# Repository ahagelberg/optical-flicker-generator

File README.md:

# Optical Flicker Generator

Optical Flicker Generator is a complete hardware + firmware device for controlled high-power optical stimulation.

Current hardware platform:

- Arduino MKR Zero
- Arduino Ethernet Shield
- Custom PCB with high-current LED driver stages

Current software provides:

- Web control page (`/`)
- Web configuration page (`/config`)
- HTTP JSON API
- ASCII shell over Serial and optional Telnet

## Project Scope

- Firmware source code is under `firmware/`.
- Hardware design files (schematics/PCB/manufacturing outputs) are under `hardware/`.

## Documentation

- User manual: `firmware/USER_MANUAL.md`
- Interface/protocol reference: `firmware/PROTOCOL.md`

## Getting Started

1. Flash the firmware to the device.
2. Connect power and Ethernet.
3. Open the control page in a browser using:
   - `http://flicker-<suffix>.local/`, or
   - the IP shown on the device display.

## Repository Layout

- `firmware/` - PlatformIO firmware source and documentation
- `hardware/` - Hardware design files

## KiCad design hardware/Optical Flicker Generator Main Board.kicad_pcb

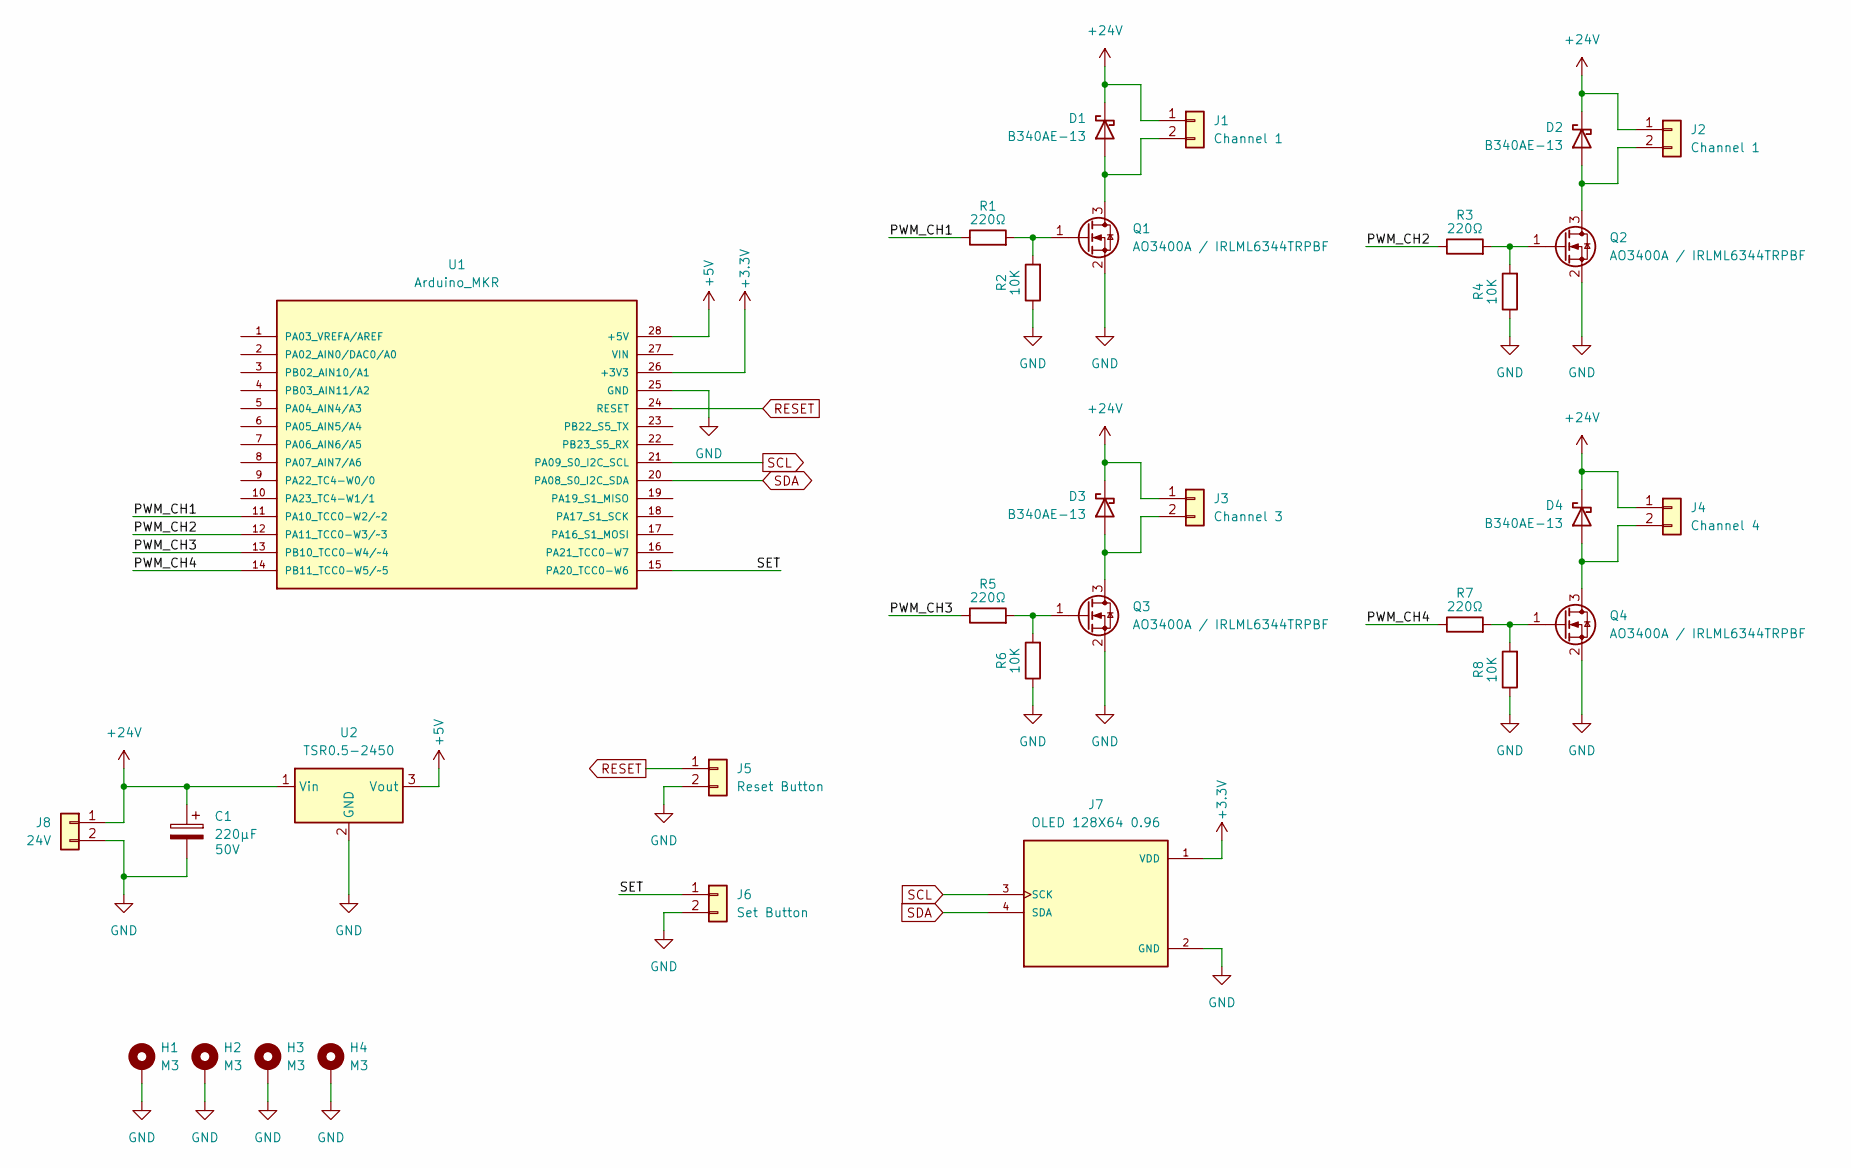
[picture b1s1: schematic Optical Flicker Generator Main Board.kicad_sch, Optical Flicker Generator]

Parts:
C1: 220μF; CP_Elec_10x10.5; Voltage 50V
D1, D2, D3, D4: B340AE-13; D_SMA
H1, H2, H3, H4: M3; MountingHole_3.2mm_M3_Pad
J1, J2: Channel 1; JST_XH_B2B-XH-A_1x02_P2.50mm_Vertical
J3: Channel 3; JST_XH_B2B-XH-A_1x02_P2.50mm_Vertical
J4: Channel 4; JST_XH_B2B-XH-A_1x02_P2.50mm_Vertical
J5: Reset Button; JST_XH_B2B-XH-A_1x02_P2.50mm_Vertical
J6: Set Button; JST_XH_B2B-XH-A_1x02_P2.50mm_Vertical
J7: OLED 128X64 0.96; JST_XH_B4B-XH-A_1x04_P2.50mm_Vertical; PARTREV NA
J8: 24V; JST_XH_B2B-XH-A_1x02_P2.50mm_Vertical
Q1, Q2, Q3, Q4: AO3400A / IRLML6344TRPBF; SOT-23
R1, R3, R5, R7: 220Ω; R_0805_2012Metric
R2, R4, R6, R8: 10K; R_0805_2012Metric
U1: Arduino_MKR; PARTREV 5
U2: TSR0.5-2450; Converter_DCDC_TRACO_TSR0.5-24xx_TSR0.5-24xxx_THT

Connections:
+3.3V: J7.1 (VDD), U1.26 (+3V3)
+5V: U1.28 (+5V), U2.3 (Vout)
+24V: C1.1, D1.1 (K), D2.1 (K), D3.1 (K), D4.1 (K), J1.1, J2.1, J3.1, J4.1, J8.1, U2.1 (Vin)
/PWM_CH1: R1.1, U1.11 (PA10_TCC0-W2/~2)
/PWM_CH2: R3.1, U1.12 (PA11_TCC0-W3/~3)
/PWM_CH3: R5.1, U1.13 (PB10_TCC0-W4/~4)
/PWM_CH4: R7.1, U1.14 (PB11_TCC0-W5/~5)
/SET: J6.1, U1.15 (PA20_TCC0-W6)
GND: C1.2, H1.1 (1_1), H2.1 (1_1), H3.1 (1_1), H4.1 (1_1), J5.2, J6.2, J7.2 (GND), J8.2, Q1.2 (S), Q2.2 (S), Q3.2 (S), Q4.2 (S), R2.1, R4.1, R6.1, R8.1, U1.25 (GND), U2.2 (GND)
unnamed: D1.2 (A), J1.2, Q1.3 (D)
unnamed: D2.2 (A), J2.2, Q2.3 (D)
unnamed: D3.2 (A), J3.2, Q3.3 (D)
unnamed: D4.2 (A), J4.2, Q4.3 (D)
unnamed: Q1.1 (G), R1.2, R2.2
unnamed: Q2.1 (G), R3.2, R4.2
unnamed: Q3.1 (G), R5.2, R6.2
unnamed: Q4.1 (G), R7.2, R8.2
RESET: J5.1, U1.24 (RESET)
SCL: J7.3 (SCK), U1.21 (PA09_S0_I2C_SCL)
SDA: J7.4 (SDA), U1.20 (PA08_S0_I2C_SDA)

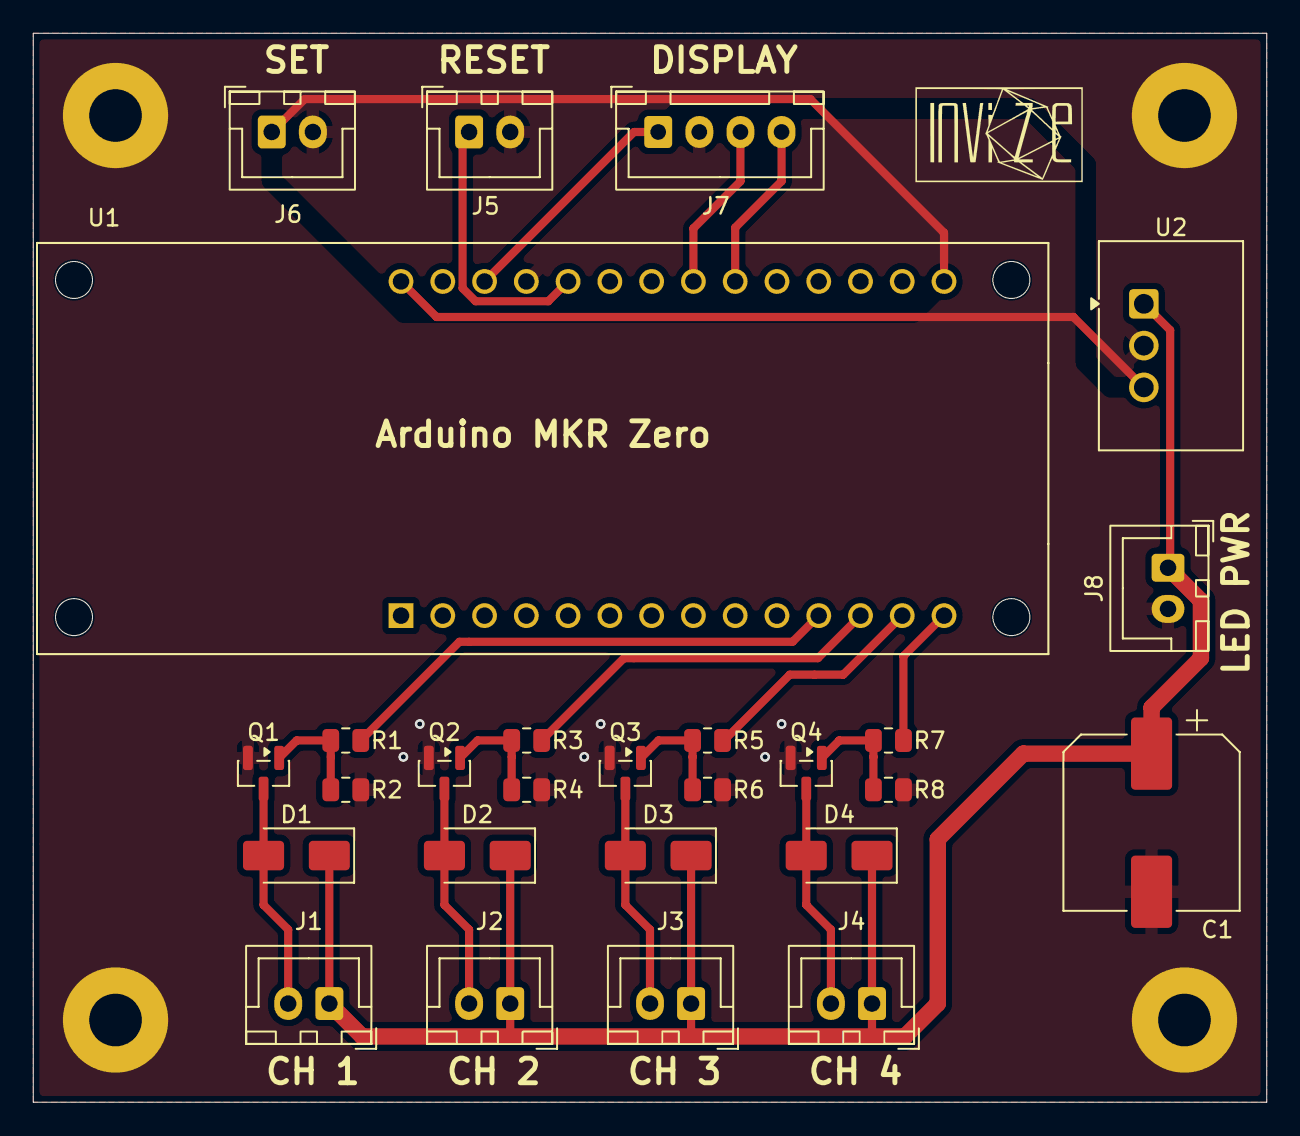
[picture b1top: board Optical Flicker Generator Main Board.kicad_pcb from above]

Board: 2 copper layers, 75.0 x 65.0 mm, 33 parts (1 on the bottom side), 20 nets.

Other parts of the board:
Ref**: Val**; Invize logo 10x6 - no tagline - Back
Ref**#2: Val**; Invize logo 10x6 - no tagline - Back

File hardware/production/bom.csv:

Designator,Footprint,Quantity,Value,LCSC Part #
C1,CP_Elec_10x10.5,1,470μF,
"D1, D2, D3, D4",D_SMA,4,D_Schottky,
"J1, J2, J3, J4",JST_XH_B2B-XH-A_1x02_P2.50mm_Vertical,4,Channel 1,
J5,JST_XH_B2B-XH-A_1x02_P2.50mm_Vertical,1,Reset Button,
J6,JST_XH_B2B-XH-A_1x02_P2.50mm_Vertical,1,Set Button,
J7,JST_XH_B4B-XH-A_1x04_P2.50mm_Vertical,1,OLED 128X64 0.96,
J8,JST_XH_B2B-XH-A_1x02_P2.50mm_Vertical,1,24V,
"Q1, Q2, Q3, Q4",SOT-23,4,AO3400A / IRLML6344TRPBF,
"R1, R3, R5, R7",0805,4,220Ω,
"R2, R4, R6, R8",0805,4,10K,
U1,Arduino_MKR,1,Arduino_MKR,
U2,Converter_DCDC_TRACO_TSR0.5-24xx_TSR0.5-24xxx_THT,1,TSR0.5-2450,

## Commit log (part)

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2026-05-01 First version. Fully featured.
2026-06-01 Added mDNS discovery
2026-06-01 Updated name of device in web pages.
2026-06-02 Moved firmware into separate folder so hardware design can be added to repo.
2026-06-02 Added static IP config options. Added telnet enable/disable config - disable by default.
2026-06-02 Updated protocol description to be accurate and useful for integrator.
2026-06-02 Added basic user manual.
2026-06-02 Added manuals in PDF format.
